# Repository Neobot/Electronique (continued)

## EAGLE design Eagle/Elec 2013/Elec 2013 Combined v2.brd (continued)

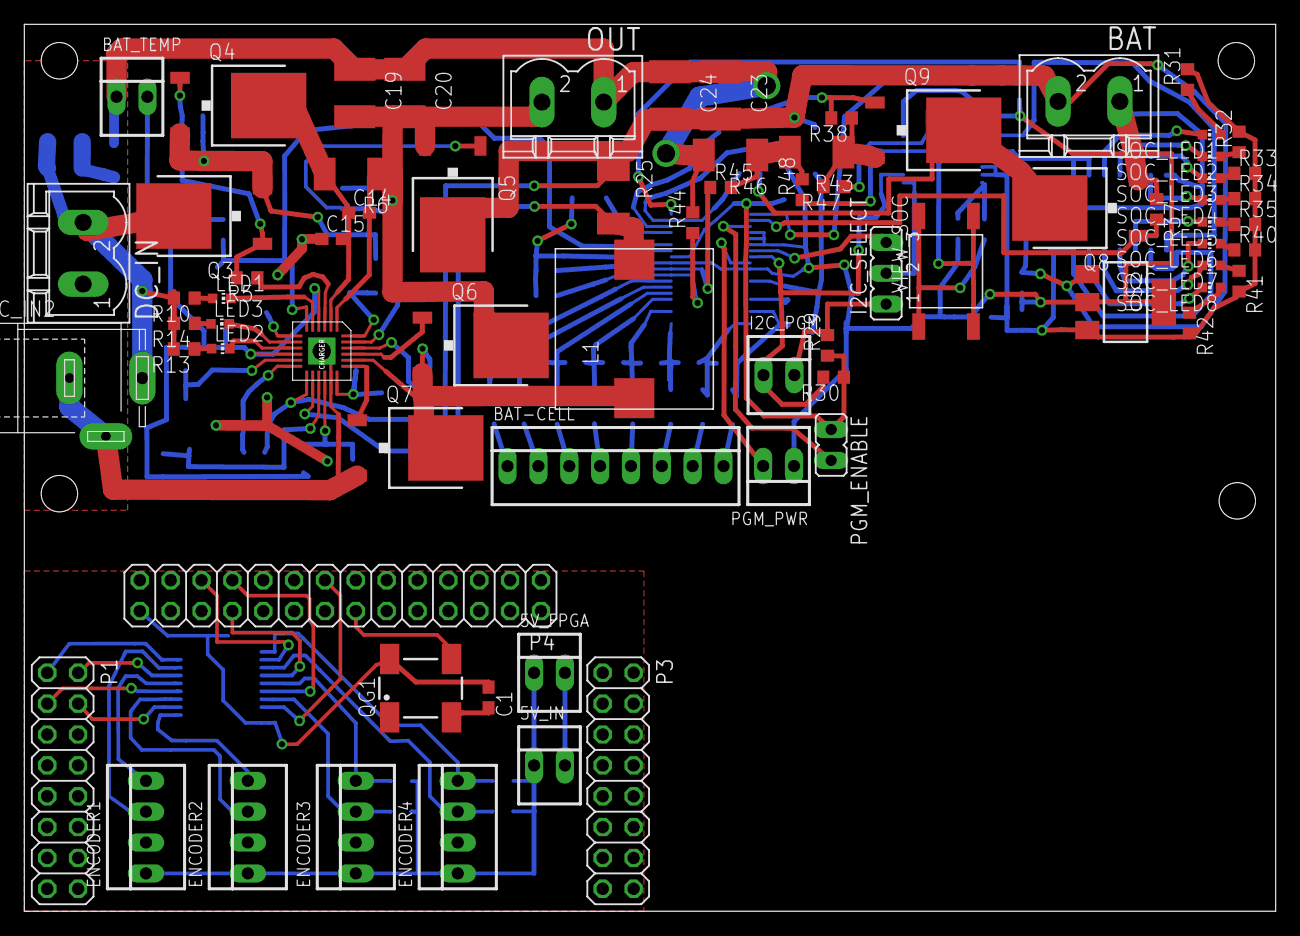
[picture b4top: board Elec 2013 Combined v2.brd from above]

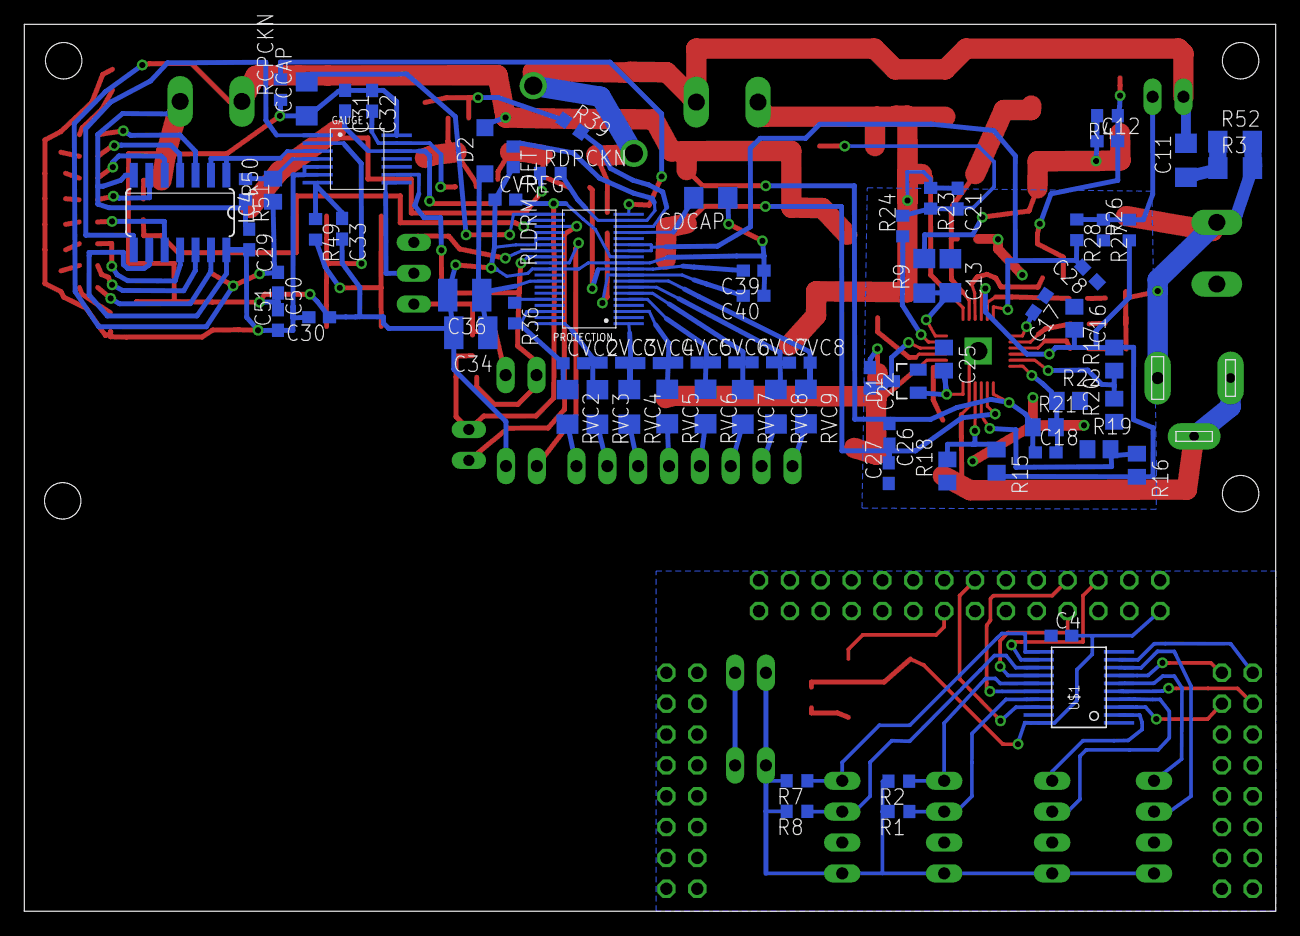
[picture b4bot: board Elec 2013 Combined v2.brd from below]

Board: 2 copper layers, 103.0 x 73.0 mm, 150 parts (77 on the bottom side), 115 nets.

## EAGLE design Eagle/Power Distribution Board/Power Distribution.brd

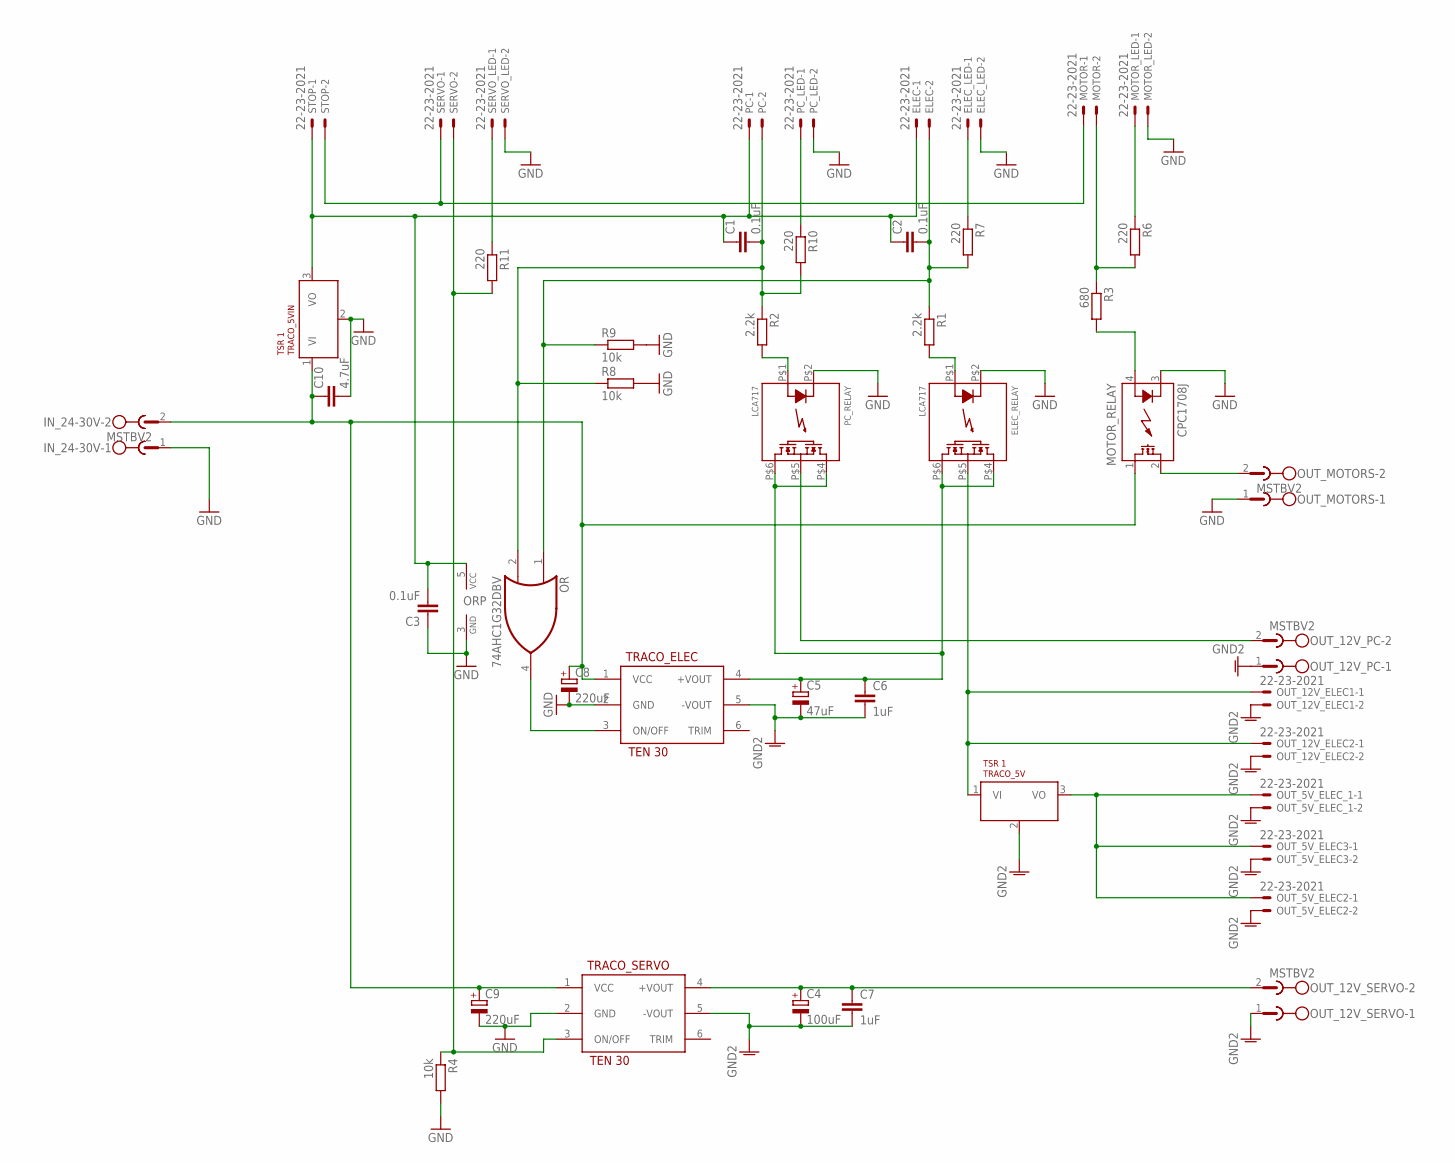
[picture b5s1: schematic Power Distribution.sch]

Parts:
C1, C2, C3: 0.1uF; C0805
C4: 100uF; E2-5
C5: 47uF; E2-5
C6, C7: 1uF; C1206
C8, C9: 220uF; E3,5-8
C10: 4.7uF; C1210
ELEC: 22-23-2021
ELEC_LED: 22-23-2021
ELEC_RELAY: LCA717; DIP-6
IN_24-30V: MSTBV2
MOTOR: 22-23-2021
MOTOR_LED: 22-23-2021
MOTOR_RELAY: CPC1708J; I4-PAC
OR: 74AHC1G32DBV; SOT23-5
OUT_5V_ELEC2, OUT_5V_ELEC3, OUT_5V_ELEC_1, OUT_12V_ELEC1, OUT_12V_ELEC2: 22-23-2021
OUT_12V_PC, OUT_12V_SERVO: MSTBV2
OUT_MOTORS: MSTBV2
PC: 22-23-2021
PC_LED: 22-23-2021
PC_RELAY: LCA717; DIP-6
R1, R2: 2.2k; R0805
R3: 680; R0805
R4, R8, R9: 10k; R0805
R6, R7, R10, R11: 220; R0805
SERVO: 22-23-2021
SERVO_LED: 22-23-2021
STOP: 22-23-2021
TRACO_5V, TRACO_5VIN: TSR-1; TRACO-TO220
TRACO_ELEC: TEN-30; TRACO2X1
TRACO_SERVO: TEN-50; TRACO2X1

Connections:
5V: C1.1, C2.1, C3.2, ELEC.1, OR.5 (VCC), PC.1, STOP.1, TRACO_5VIN.3 (VO)
AGND: C4.-, C5.-, C6.2, C7.2, OUT_5V_ELEC2.2, OUT_5V_ELEC3.2, OUT_5V_ELEC_1.2, OUT_12V_ELEC1.2, OUT_12V_ELEC2.2, OUT_12V_PC.1, OUT_12V_SERVO.1, TRACO_5V.2 (GND), TRACO_ELEC.5 (-VOUT), TRACO_SERVO.5 (-VOUT)
GND: C3.1, C8.-, C9.-, C10.2, ELEC_LED.2, ELEC_RELAY.P$2 (2), IN_24-30V.1, MOTOR_LED.2, MOTOR_RELAY.3 (K), OR.3 (GND), OUT_MOTORS.1, PC_LED.2, PC_RELAY.P$2 (2), R4.2, R8.2, R9.2, SERVO_LED.2, TRACO_5VIN.2 (GND), TRACO_ELEC.2 (GND), TRACO_SERVO.2 (GND)
unnamed: C8.+, C9.+, C10.1, IN_24-30V.2, MOTOR_RELAY.1 (DS1), TRACO_5VIN.1 (VI), TRACO_ELEC.1 (VCC), TRACO_SERVO.1 (VCC)
unnamed: C4.+, C7.1, OUT_12V_SERVO.2, TRACO_SERVO.4 (+VOUT)
unnamed: MOTOR_RELAY.2 (DS2), OUT_MOTORS.2
unnamed: MOTOR_LED.1, R6.1
unnamed: ELEC_RELAY.P$5 (5), OUT_12V_ELEC1.1, OUT_12V_ELEC2.1, TRACO_5V.1 (VI)
unnamed: OUT_5V_ELEC2.1, OUT_5V_ELEC3.1, OUT_5V_ELEC_1.1, TRACO_5V.3 (VO)
unnamed: OUT_12V_PC.2, PC_RELAY.P$5 (5)
unnamed: C5.+, C6.1, ELEC_RELAY.P$4 (4), ELEC_RELAY.P$6 (6), PC_RELAY.P$4 (4), PC_RELAY.P$6 (6), TRACO_ELEC.4 (+VOUT)
unnamed: MOTOR_RELAY.4 (A), R3.2
unnamed: ELEC_RELAY.P$1 (1), R1.2
unnamed: R4.1, R11.2, SERVO.2, TRACO_SERVO.3 (ON/OFF)
unnamed: C1.2, OR.2 (I1), PC.2, R2.1, R8.1, R10.2
unnamed: C2.2, ELEC.2, OR.1 (I0), R1.1, R7.2, R9.1
unnamed: MOTOR.2, R3.1, R6.2
unnamed: MOTOR.1, SERVO.1, STOP.2
unnamed: PC_RELAY.P$1 (1), R2.2
unnamed: OR.4 (O), TRACO_ELEC.3 (ON/OFF)
unnamed: PC_LED.1, R10.1
unnamed: R11.1, SERVO_LED.1
unnamed: ELEC_LED.1, R7.1

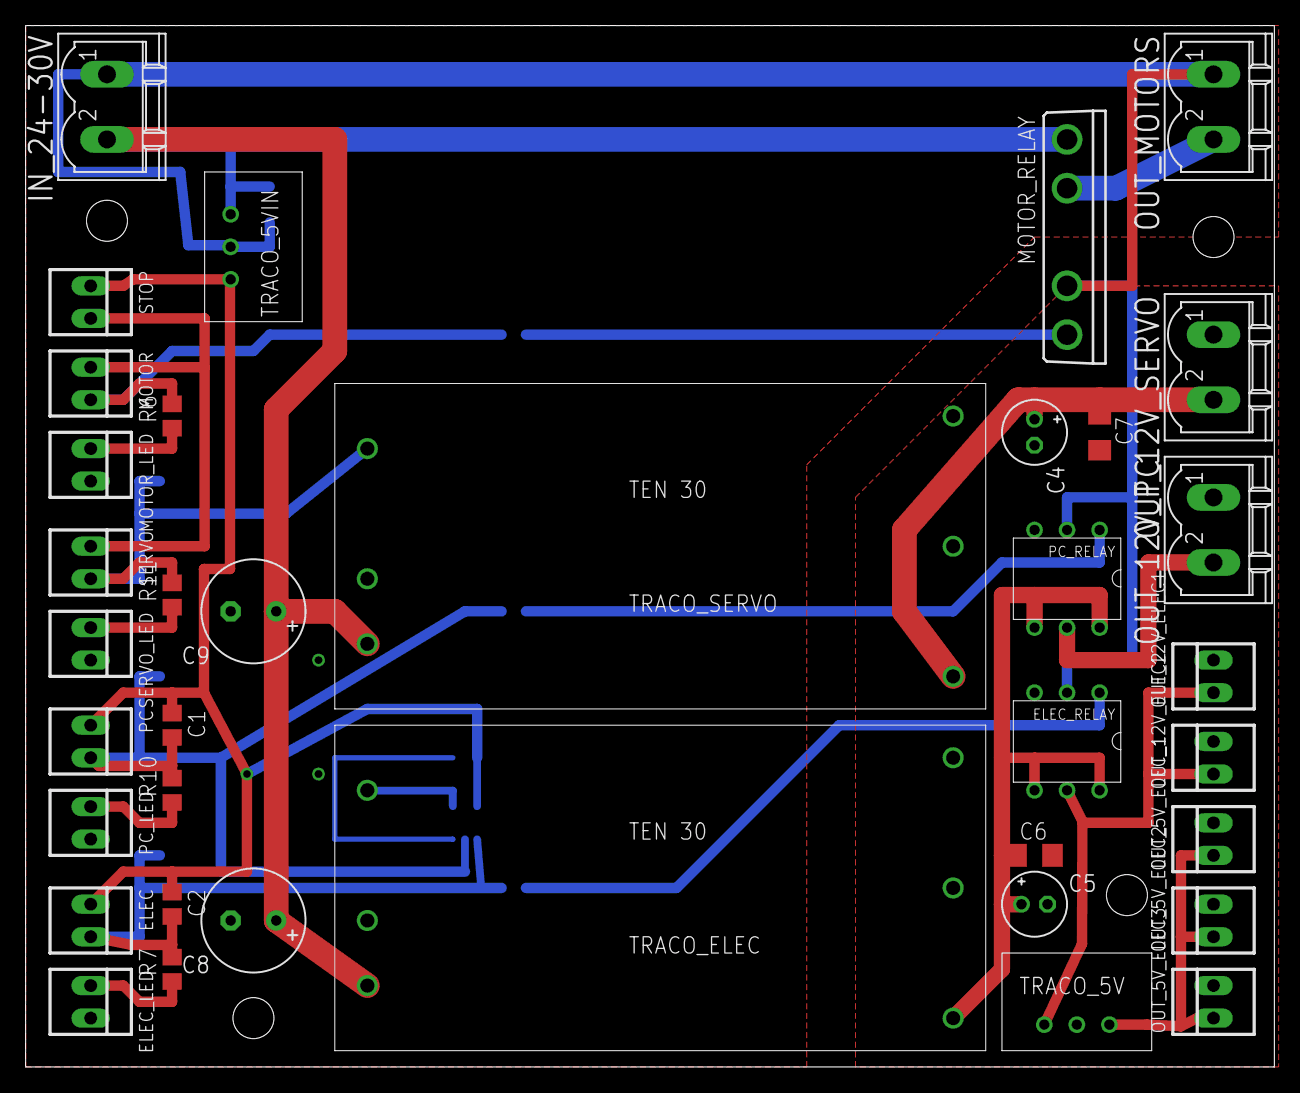
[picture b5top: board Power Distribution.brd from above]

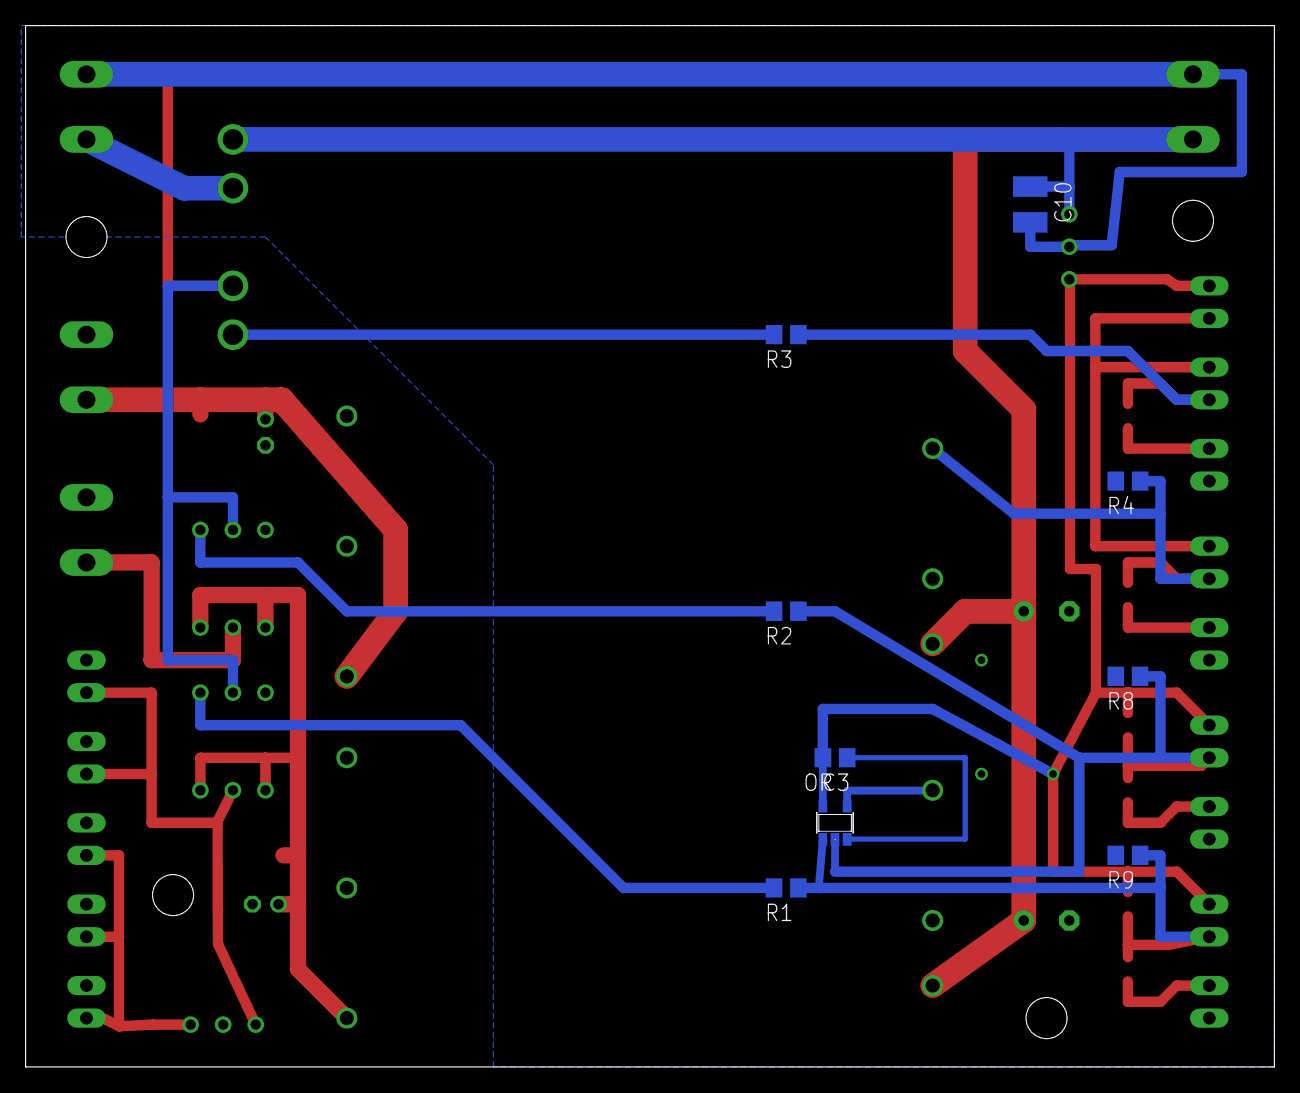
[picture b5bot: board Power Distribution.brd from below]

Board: 2 copper layers, 97.5 x 81.3 mm, 46 parts (9 on the bottom side), 23 nets.
